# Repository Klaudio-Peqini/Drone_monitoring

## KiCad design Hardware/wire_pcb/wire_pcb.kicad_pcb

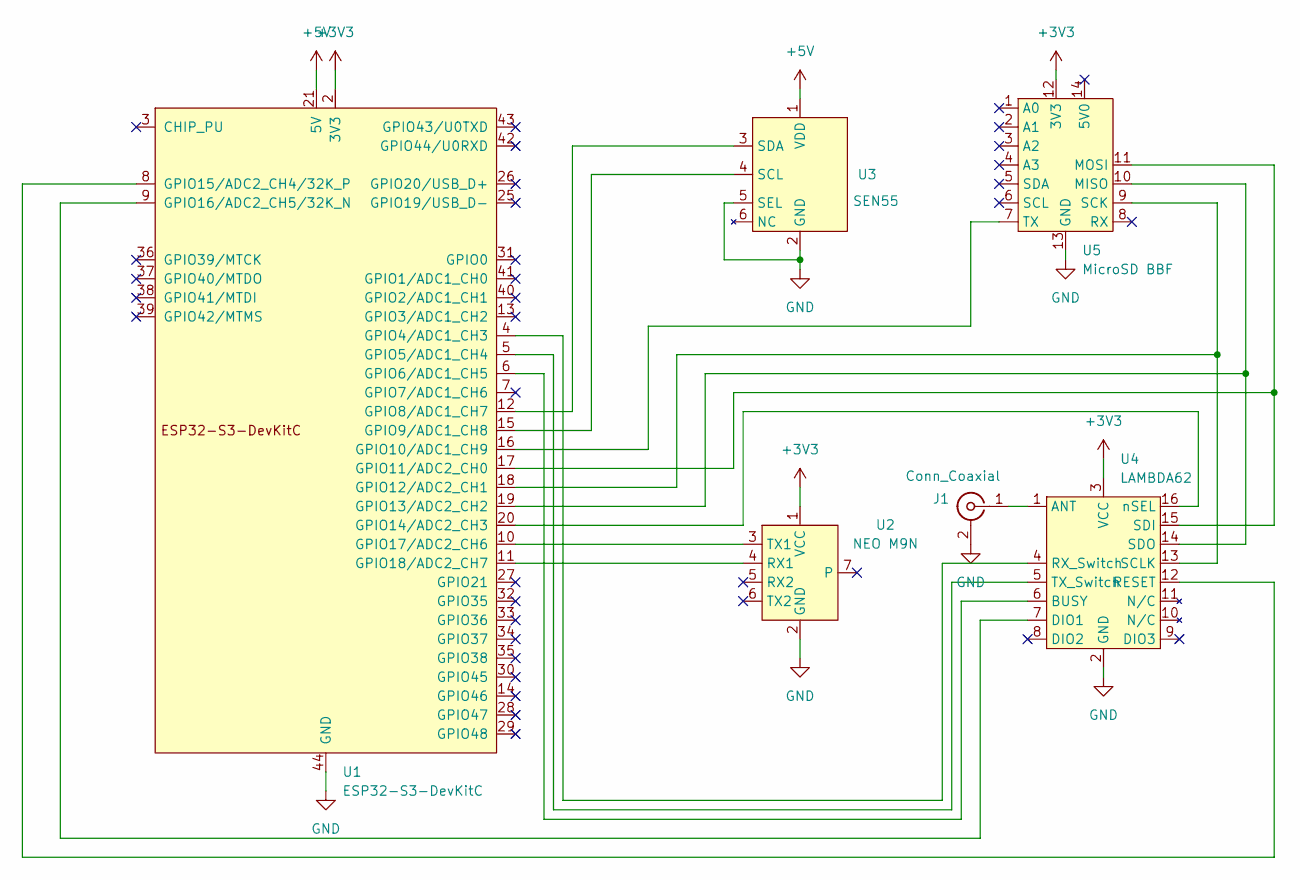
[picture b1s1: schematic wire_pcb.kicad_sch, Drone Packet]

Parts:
J1: Conn_Coaxial; U.FL_Hirose_U.FL-R-SMT-1_Vertical
U1: ESP32-S3-DevKitC
U2: NEO M9N
U3: SEN55
U4: LAMBDA62
U5: MicroSD BBF; MicroSD_BBF

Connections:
+3V3: U1.1 (3V3), U1.2 (3V3), U2.1 (VCC), U4.3 (VCC), U5.12 (3V3)
+5V: U1.21 (5V), U3.1 (VDD)
GND: J1.2 (Ext), U1.22 (GND), U1.23 (GND), U1.24 (GND), U1.44 (GND), U2.2 (GND), U3.2 (GND), U3.5 (SEL), U4.2 (GND), U5.13 (GND)
unnamed: J1.1 (In), U4.1 (ANT)
unnamed: U1.4 (GPIO4/ADC1_CH3), U4.4 (RX_Switch)
unnamed: U1.5 (GPIO5/ADC1_CH4), U4.5 (TX_Switch)
unnamed: U1.6 (GPIO6/ADC1_CH5), U4.6 (BUSY)
unnamed: U1.12 (GPIO8/ADC1_CH7), U3.3 (SDA)
unnamed: U1.15 (GPIO9/ADC1_CH8), U3.4 (SCL)
unnamed: U1.16 (GPIO10/ADC1_CH9), U5.7 (TX)
unnamed: U1.17 (GPIO11/ADC2_CH0), U4.15 (SDI), U5.11 (MOSI)
unnamed: U1.18 (GPIO12/ADC2_CH1), U4.13 (SCLK), U5.9 (SCK)
unnamed: U1.19 (GPIO13/ADC2_CH2), U4.14 (SDO), U5.10 (MISO)
unnamed: U1.20 (GPIO14/ADC2_CH3), U4.16 (nSEL)
unnamed: U1.8 (GPIO15/ADC2_CH4/32K_P), U4.12 (RESET)
unnamed: U1.9 (GPIO16/ADC2_CH5/32K_N), U4.7 (DIO1)
unnamed: U1.10 (GPIO17/ADC2_CH6), U2.3 (TX1)
unnamed: U1.11 (GPIO18/ADC2_CH7), U2.4 (RX1)

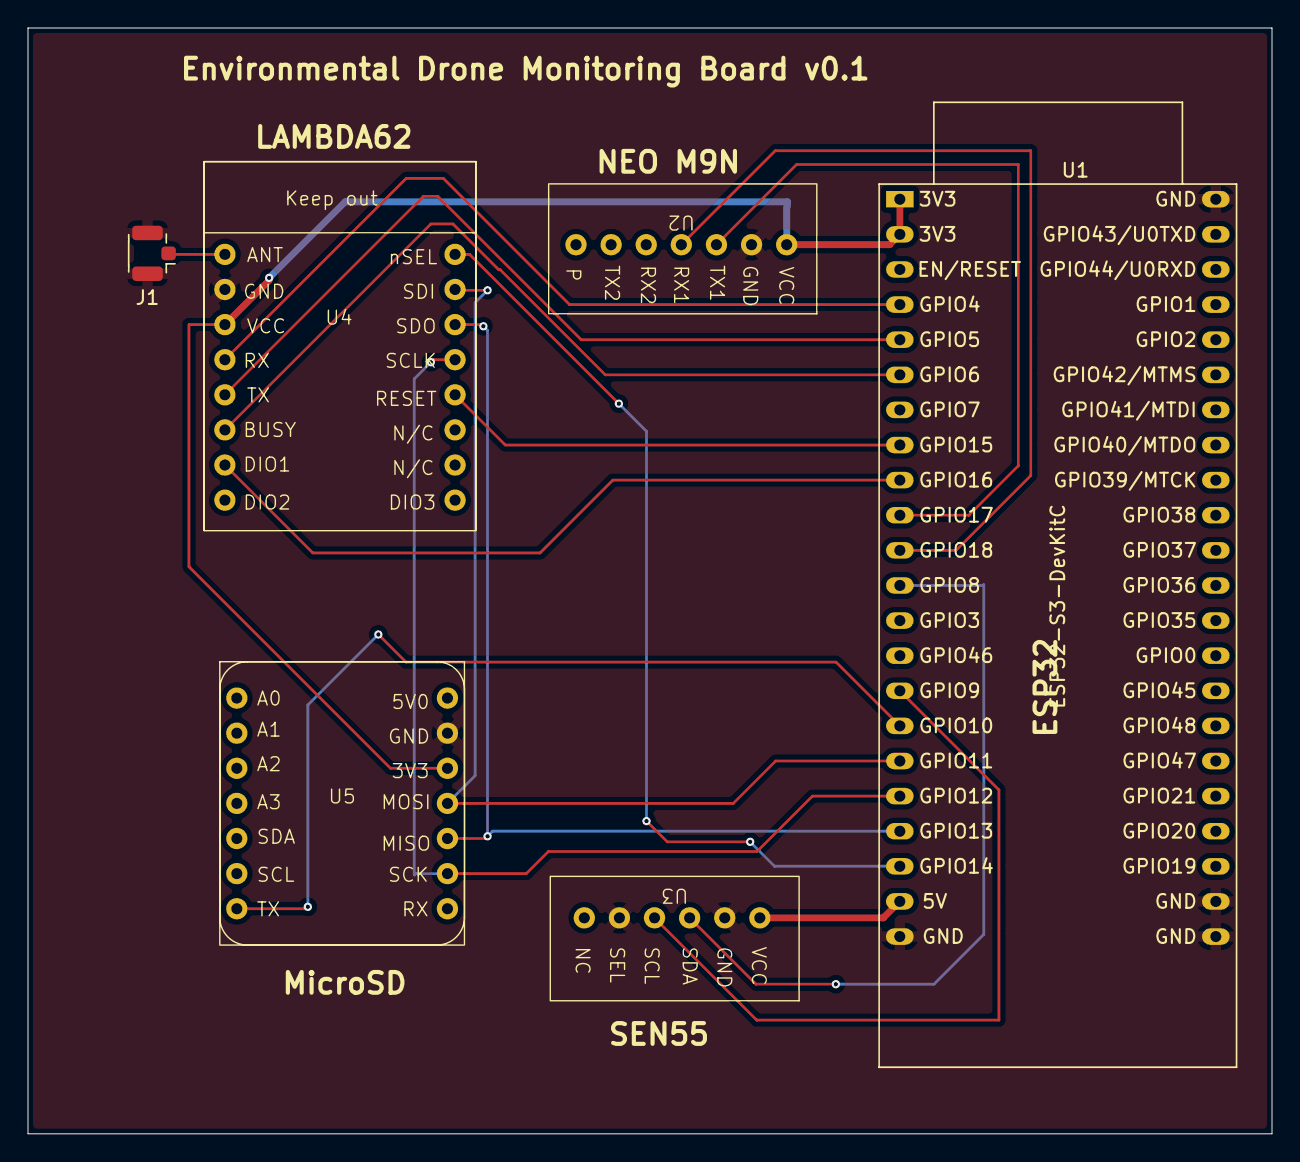
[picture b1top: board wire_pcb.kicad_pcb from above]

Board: 2 copper layers, 90.0 x 80.0 mm, 6 parts (0 on the bottom side), 18 nets.
